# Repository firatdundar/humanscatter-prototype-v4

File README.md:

# Humanscatter v4 — Low-Power Backscatter Wireless Communication Prototype  
**Summer Research Project at RISE Research Institutes of Sweden**  

Humanscatter v4 is an **enhanced version** of the [original Humanscatter project](https://github.com/amau75/Humanscatter), developed as part of a **summer research internship** at **RISE Research Institutes of Sweden**.  
This work focuses on **improving the range, reliability, and power stability** of a **low-power backscatter wireless communication prototype** for battery-free IoT applications.

---

## What's New in Humanscatter v4

### **v4.1**
- **Carrier module upgraded** to an **ADF4351 RF synthesizer** instead of CC2500.
- Added **AMS1117 3.3 V LDO regulator** for **cleaner and more stable power**.
- Improved range thanks to **better carrier control** and lower noise.
- Redesigned **KiCad PCB design** and updated **Raspberry Pi Pico firmware**.

### **v4.2**
- Built on top of v4.1 enhancements.
- **Receiver module upgraded** to a **CC2500 EMK evaluation kit**.
- Switched from a **trace antenna** to an **SMA-based external antenna** for better sensitivity.
- **AMS1117 regulator retained** for stable RF power delivery.
- Further improved range, carrier stability, and signal reliability.

---

## Hardware Overview

| Component            | Original                    | v4.1                               | v4.2                                 |
|----------------------|-----------------------------|-------------------------------------|--------------------------------------|
| **Carrier Module**   | CC2500                      | **ADF4351** (RF synthesizer)        | **ADF4351** (RF synthesizer)        |
| **Receiver Module**  | CC2500 (trace antenna)      | CC2500 (trace antenna)             | **CC2500 EMK** + **SMA antenna**    |
| **Voltage Regulator**| None                        | **AMS1117 (3.3 V LDO)**            | **AMS1117 (3.3 V LDO)**            |
| **Microcontroller**  | Raspberry Pi Pico          | Raspberry Pi Pico                  | Raspberry Pi Pico                  |
| **Antenna Type**     | Trace PCB antenna          | Trace PCB antenna                  | **SMA external antenna**           |
| **PCB Design**       | Original Humanscatter PCB  | Updated KiCad design               | Updated KiCad design               |

---

## Repository Structure

```

humanscatter-v4/
│
├── humanscatter-v4.1/
│   ├── kicad/           # KiCad schematic + PCB files for v4.1
│   └── firmware/        # Updated Raspberry Pi Pico code for v4.1
│
├── humanscatter-v4.2/
│   ├── kicad/           # KiCad schematic + PCB files for v4.2
│   └── firmware/        # Updated Raspberry Pi Pico code for v4.2
│
└── README.md            # This file

````

---

## Getting Started

### 1. Clone the Repository
```bash
git clone https://github.com/yourusername/humanscatter-v4.git
cd humanscatter-v4
````

### 2. Open KiCad Project

```bash
cd humanscatter-v4.1/kicad
open humanscatter-v4.1.kicad_pro
```

*(Same for `humanscatter-v4.2`.)*

### 3. Build and Flash Firmware

* Follow the same steps as in the [original Humanscatter project](https://github.com/amau75/Humanscatter).
* Replace the firmware files with the updated ones provided in the **`firmware/`** folder.
* Flash the code to the **Raspberry Pi Pico** using **Thonny** or any other MicroPython flashing tool.

##  Experimental Improvements

The key goals of this research were to **improve range**, **stability**, and **power delivery**.
Using the **ADF4351 RF synthesizer**, **AMS1117 regulator**, and an **SMA-based CC2500 EMK receiver**:

* Achieved **greater link distance** compared to original version.
* Improved **signal-to-noise ratio (SNR)**.
* Reduced **carrier frequency drift**.
* Increased **overall communication reliability**.

---

## License

This project builds upon the original [Humanscatter](https://github.com/amau75/Humanscatter)
and is released under the **CERN-OHL-P** open hardware license.

---

## Acknowledgements

* **Dr. Fehmi Ben Abdesslem** — for supervision and continuous support throughout the summer research
* **Amaury Couderc** — for the original Humanscatter project and guidance
* **RISE Research Institutes of Sweden** — for hosting and supporting the project

---

## 🔗 References

* Original Humanscatter repository: [https://github.com/amau75/Humanscatter](https://github.com/amau75/Humanscatter)
* ADF4351 RF Synthesizer Module: [Datasheet](https://www.analog.com/media/en/technical-documentation/data-sheets/ADF4351.pdf)
* CC2500 RF Transceiver: [Datasheet](https://www.ti.com/product/CC2500)
* AMS1117 Voltage Regulator: [Datasheet](http://www.advanced-monolithic.com/pdf/ds1117.pdf)

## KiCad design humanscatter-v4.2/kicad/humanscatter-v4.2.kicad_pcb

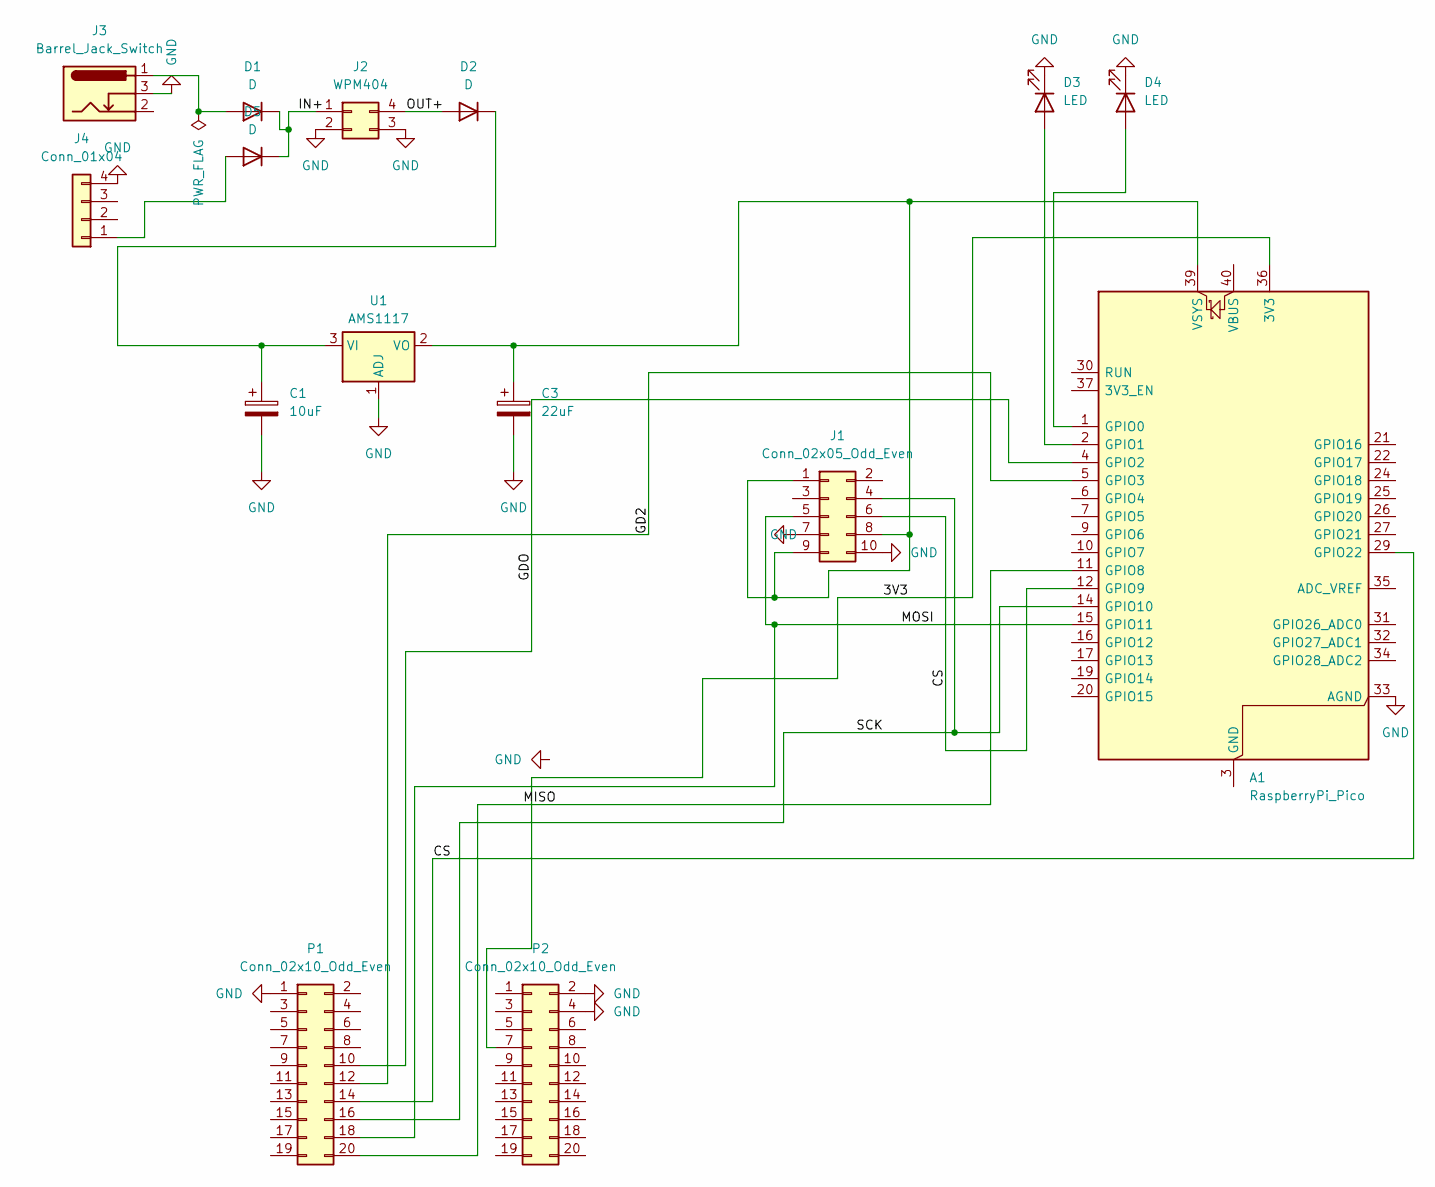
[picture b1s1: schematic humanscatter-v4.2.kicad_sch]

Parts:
A1: RaspberryPi_Pico; RaspberryPi_Pico_Common_THT
C1: 10uF; CP_Elec_6.3x5.4
C3: 22uF; CP_Elec_5x5.4
D1, D2, D5: D; D_SMA_Handsoldering
D3, D4: LED; LED_D5.0mm
J1: Conn_02x05_Odd_Even; PinSocket_2x05_P2.54mm_Vertical
J2: WPM404; WPM404_New
J3: Barrel_Jack_Switch; BarrelJack_Wuerth_6941xx301002
J4: Conn_01x04; PinHeader_1x04_P2.54mm_Vertical
P1, P2: Conn_02x10_Odd_Even; PinHeader_2x10_P1.27mm_Vertical
U1: AMS1117; SOT-223-3_TabPin2

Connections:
/3V3: A1.36 (3V3), P2.7
/CS: A1.12 (GPIO9), A1.29 (GPIO22), J1.6, P1.14
/GD2: A1.5 (GPIO3), P1.12
/GDO: A1.4 (GPIO2), P1.10
/IN+: D1.1 (K), D5.1 (K), J2.1
/MISO: A1.11 (GPIO8), P1.20
/MOSI: A1.15 (GPIO11), J1.5, P1.18
/OUT+: D2.2 (A), J2.4
/SCK: A1.14 (GPIO10), J1.4, P1.16
GND: A1.33 (AGND), C1.2, C3.2, D3.1 (K), D4.1 (K), J1.7, J1.10, J2.2, J2.3, J3.3, J4.4, P1.1, P2.2, P2.4, U1.1 (ADJ)
unnamed: A1.3 (GND), A1.8 (GND), A1.13 (GND), A1.18 (GND), A1.23 (GND), A1.28 (GND), A1.38 (GND)
unnamed: A1.1 (GPIO0), D4.2 (A)
unnamed: A1.2 (GPIO1), D3.2 (A)
unnamed: A1.39 (VSYS), C3.1, J1.1, J1.8, J1.9, U1.2 (VO)
unnamed: D1.2 (A), J3.1
unnamed: C1.1, D2.1 (K), U1.3 (VI)
unnamed: D5.2 (A), J4.1

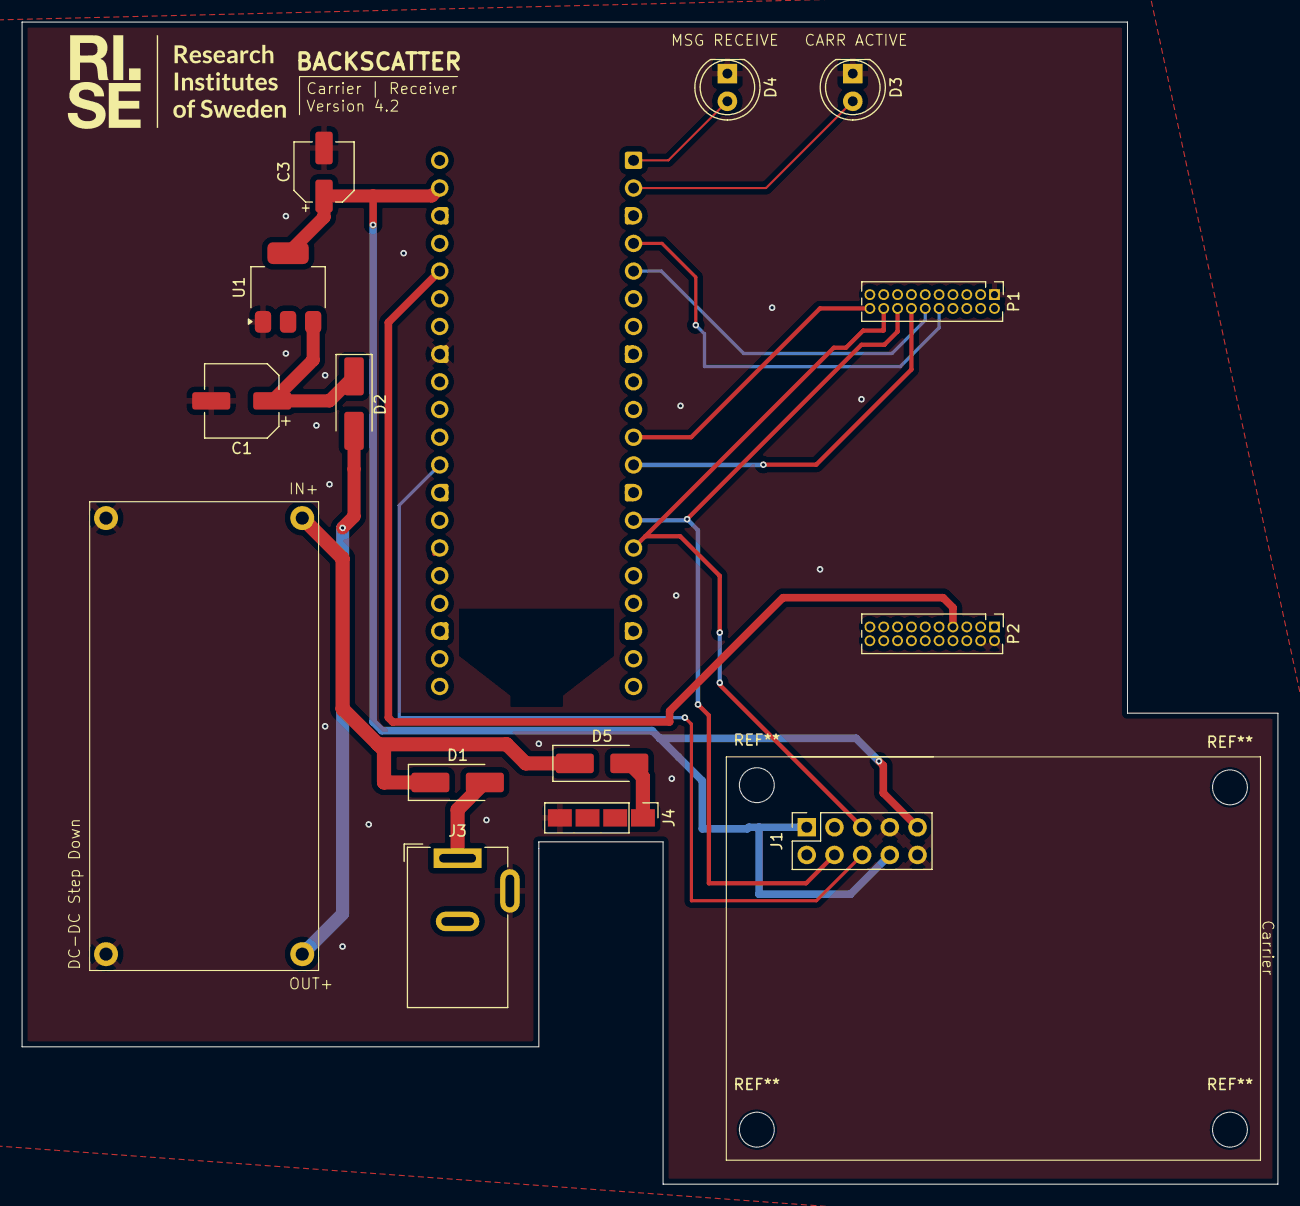
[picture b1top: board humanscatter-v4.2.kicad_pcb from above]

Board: 2 copper layers, 115.2 x 106.6 mm, 15 parts (1 on the bottom side), 17 nets.

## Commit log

2025-09-07 KiCad design files
2025-09-07 Uploaded code and updated the repo structure
2025-09-07 Updated README v2
